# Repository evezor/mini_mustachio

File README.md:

# mini_mustachio

Robotic car project for the Mechanical Mustaches, team #8122 FRC Robotics

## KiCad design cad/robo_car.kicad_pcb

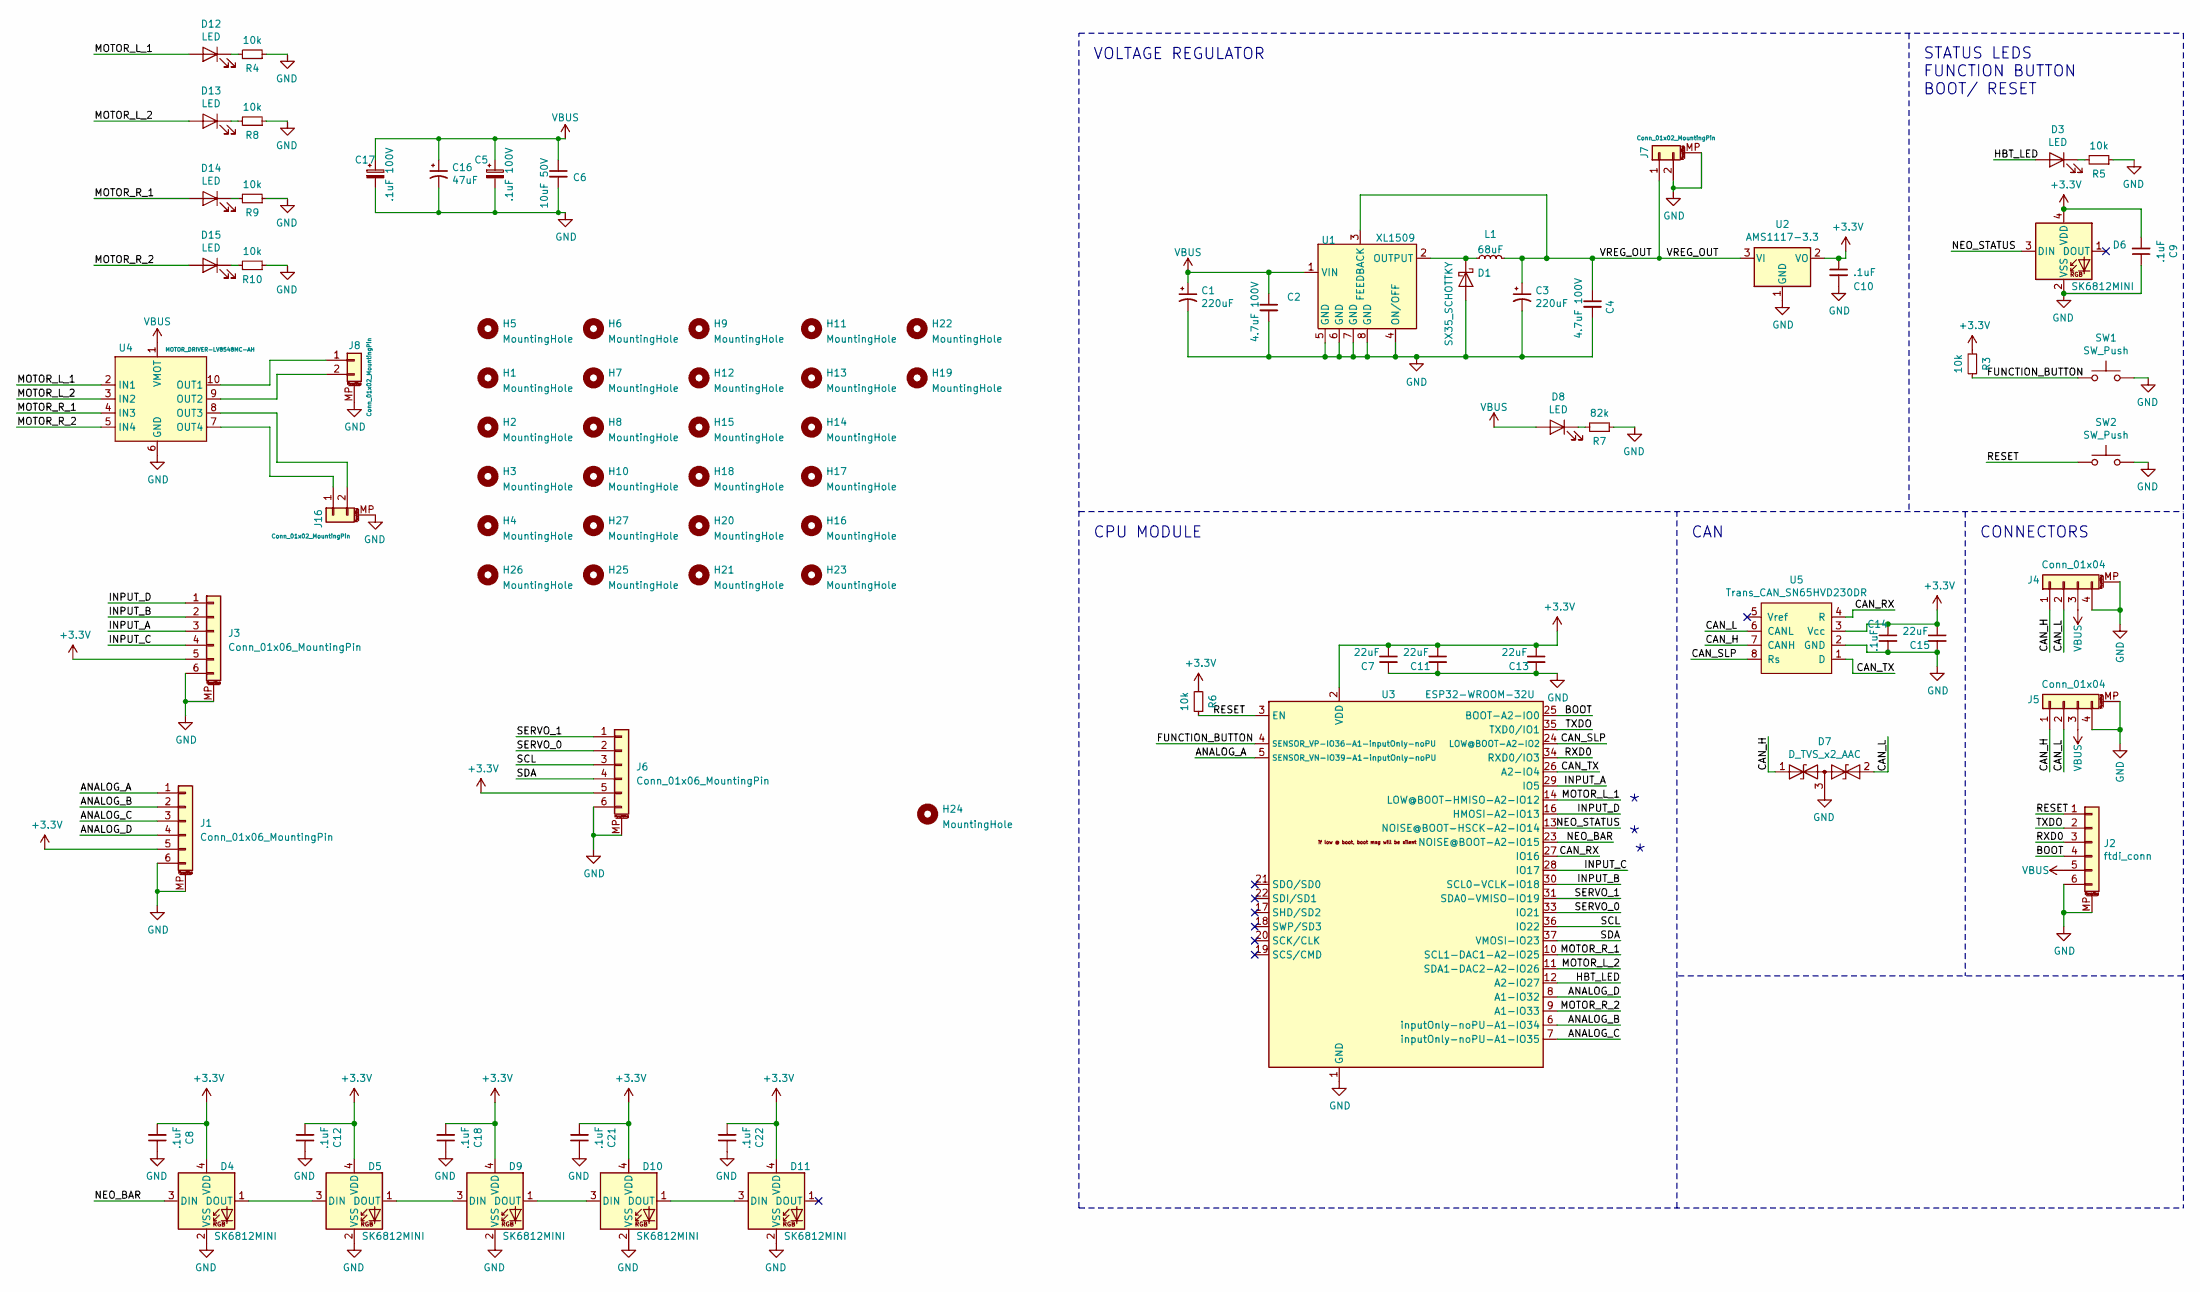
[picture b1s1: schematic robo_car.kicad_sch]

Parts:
C1, C3: 220uF; CP_Elec_10x10.5
C2, C4: 4.7uF 100V; C_0805_2012Metric
C5, C17: .1uF 100V; C_0805_2012Metric
C6: 10uF 50V; C_1206_3216Metric
C7, C11, C13, C15: 22uF; C_0805_2012Metric
C8, C9, C10, C12, C14, C18, C21, C22: .1uF; C_0603_1608Metric
C16: 47uF; CP_Elec_6.3x7.7
D1: SX35_SCHOTTKY; D_SMA
D3, D8, D12, D13, D14, D15: LED; LED_0603_1608Metric
D4, D5, D6, D9, D10, D11: SK6812MINI; LED_SK6812MINI_PLCC4_3.5x3.5mm_P1.75mm
D7: D_TVS_x2_AAC; SOT-23
H1, H2, H3, H4, H5, H6, H7, H8, H9, H10, H11, H12, H13, H14, H15, H16, H17, H18, H19, H20, H25, H26, H27: MountingHole; MountingHole_3.2mm_M3_ISO14580
H21, H22, H23, H24: MountingHole; MountingHole_2.7mm_M2.5_ISO14580
J1, J3, J6: Conn_01x06_MountingPin; TE_84952-6_1x06-1MP_P1.0mm_Horizontal
J2: ftdi_conn; JST_SH_BM06B-SRSS-TB_1x06-1MP_P1.00mm_Vertical
J4: Conn_01x04; JST_PH_B4B-PH-SM4-TB_1x04-1MP_P2.00mm_Vertical
J5: Conn_01x04; JST_PH_S4B-PH-SM4-TB_1x04-1MP_P2.00mm_Horizontal
J7, J8, J16: Conn_01x02_MountingPin; JST_XH_2_VERTICAL
L1: 68uF; INDUCTOR-68uH
R3, R4, R5, R6, R8, R9, R10: 10k; R_0603_1608Metric
R7: 82k; R_0603_1608Metric
SW1, SW2: SW_Push; SWITCH_2x3_SMD_TACTILE_GREEN
U1: XL1509; SOIC-8_3.9x4.9mm_P1.27mm
U2: AMS1117-3.3; SOT-223-3_TabPin2
U3: ESP32-WROOM-32U; ESP32-WROOM-32U_evezor
U4: MOTOR_DRIVER-LV8548MC-AH; SOIC-10_LV8548MC-AH_evezor
U5: Trans_CAN_SN65HVD230DR; CAN-TRANS-SN65HVD230DR

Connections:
+3V3: C7.1, C8.2, C9.2, C10.1, C11.1, C12.2, C13.1, C14.1, C15.1, C18.2, C21.2, C22.2, D4.4 (VDD), D5.4 (VDD), D6.4 (VDD), D9.4 (VDD), D10.4 (VDD), D11.4 (VDD), J1.5, J3.5, J6.5, R3.2, R6.2, U2.2 (VO), U3.2 (VDD), U5.3 (Vcc)
/ANALOG_A: J1.1, U3.5 (SENSOR_VN-IO39-A1-inputOnly-noPU)
/ANALOG_B: J1.2, U3.6 (inputOnly-noPU-A1-IO34)
/ANALOG_C: J1.3, U3.7 (inputOnly-noPU-A1-IO35)
/ANALOG_D: J1.4, U3.8 (A1-IO32)
/BOOT: J2.4, U3.25 (BOOT-A2-IO0)
/CAN_H: D7.1 (A1), J4.1, J5.1, U5.7 (CANH)
/CAN_L: D7.2 (A2), J4.2, J5.2, U5.6 (CANL)
/CAN_RX: U3.27 (IO16), U5.4 (R)
/CAN_SLP: U3.24 (LOW@BOOT-A2-IO2), U5.8 (Rs)
/CAN_TX: U3.26 (A2-IO4), U5.1 (D)
/FUNCTION_BUTTON: R3.1, SW1.1, U3.4 (SENSOR_VP-IO36-A1-inputOnly-noPU)
/HBT_LED: D3.2 (A), U3.12 (A2-IO27)
/INPUT_A: J3.3, U3.29 (IO5)
/INPUT_B: J3.2, U3.30 (SCL0-VCLK-IO18)
/INPUT_C: J3.4, U3.28 (IO17)
/INPUT_D: J3.1, U3.16 (HMOSI-A2-IO13)
/MOTOR_L_1: D12.2 (A), U3.14 (LOW@BOOT-HMISO-A2-IO12), U4.2 (IN1)
/MOTOR_L_2: D13.2 (A), U3.11 (SDA1-DAC2-A2-IO26), U4.3 (IN2)
/MOTOR_R_1: D14.2 (A), U3.10 (SCL1-DAC1-A2-IO25), U4.4 (IN3)
/MOTOR_R_2: D15.2 (A), U3.9 (A1-IO33), U4.5 (IN4)
/NEO_BAR: D4.3 (DIN), U3.23 (NOISE@BOOT-A2-IO15)
/NEO_STATUS: D6.3 (DIN), U3.13 (NOISE@BOOT-HSCK-A2-IO14)
/RESET: J2.1, R6.1, SW2.1, U3.3 (EN)
/RXD0: J2.3, U3.34 (RXD0/IO3)
/SCL: J6.3, U3.36 (IO22)
/SDA: J6.4, U3.37 (VMOSI-IO23)
/SERVO_0: J6.2, U3.33 (IO21)
/SERVO_1: J6.1, U3.31 (SDA0-VMISO-IO19)
/TXDO: J2.2, U3.35 (TXD0/IO1)
/VREG_OUT: C3.1, C4.1, J7.1, L1.1, U1.3 (FEEDBACK), U2.3 (VI)
GND: C1.2, C2.2, C3.2, C4.2, C5.2, C6.2, C7.2, C8.1, C9.1, C10.2, C11.2, C12.1, C13.2, C14.2, C15.2, C16.2, C17.2, C18.1, C21.1, C22.1, D1.2 (A), D4.2 (VSS), D5.2 (VSS), D6.2 (VSS), D7.3 (common), D9.2 (VSS), D10.2 (VSS), D11.2 (VSS), J1.6, J1.MP (MountPin), J2.6, J2.MP (MountPin), J3.6, J3.MP (MountPin), J4.4, J4.MP (MountPin), J5.4, J5.MP (MountPin), J6.6, J6.MP (MountPin), J7.2, J7.MP (MountPin), J8.MP (MountPin), J16.MP (MountPin), R4.1, R5.1, R7.1, R8.1, R9.1, R10.1, SW1.2, SW2.2, U1.4 (ON/OFF), U1.5 (GND), U1.6 (GND), U1.7 (GND), U1.8 (GND), U2.1 (GND), U3.1 (GND), U3.15 (GND), U3.38 (GND), U3.39 (GND), U4.6 (GND), U5.2 (GND)
unnamed: D1.1 (K), L1.2, U1.2 (OUTPUT)
unnamed: D3.1 (K), R5.2
unnamed: D4.1 (DOUT), D5.3 (DIN)
unnamed: D5.1 (DOUT), D9.3 (DIN)
unnamed: D8.1 (K), R7.2
unnamed: D10.1 (DOUT), D11.3 (DIN)
unnamed: D9.1 (DOUT), D10.3 (DIN)
unnamed: D12.1 (K), R4.2
unnamed: D13.1 (K), R8.2
unnamed: D14.1 (K), R9.2
unnamed: D15.1 (K), R10.2
unnamed: J8.1, U4.10 (OUT1)
unnamed: J8.2, U4.9 (OUT2)
unnamed: J16.1, U4.7 (OUT4)
unnamed: J16.2, U4.8 (OUT3)
VBUS: C1.1, C2.1, C5.1, C6.1, C16.1, C17.1, D8.2 (A), J2.5, J4.3, J5.3, U1.1 (VIN), U4.1 (VMOT)

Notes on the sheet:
VOLTAGE REGULATOR
CPU MODULE
CAN
STATUS LEDS FUNCTION BUTTON BOOT/ RESET
CONNECTORS

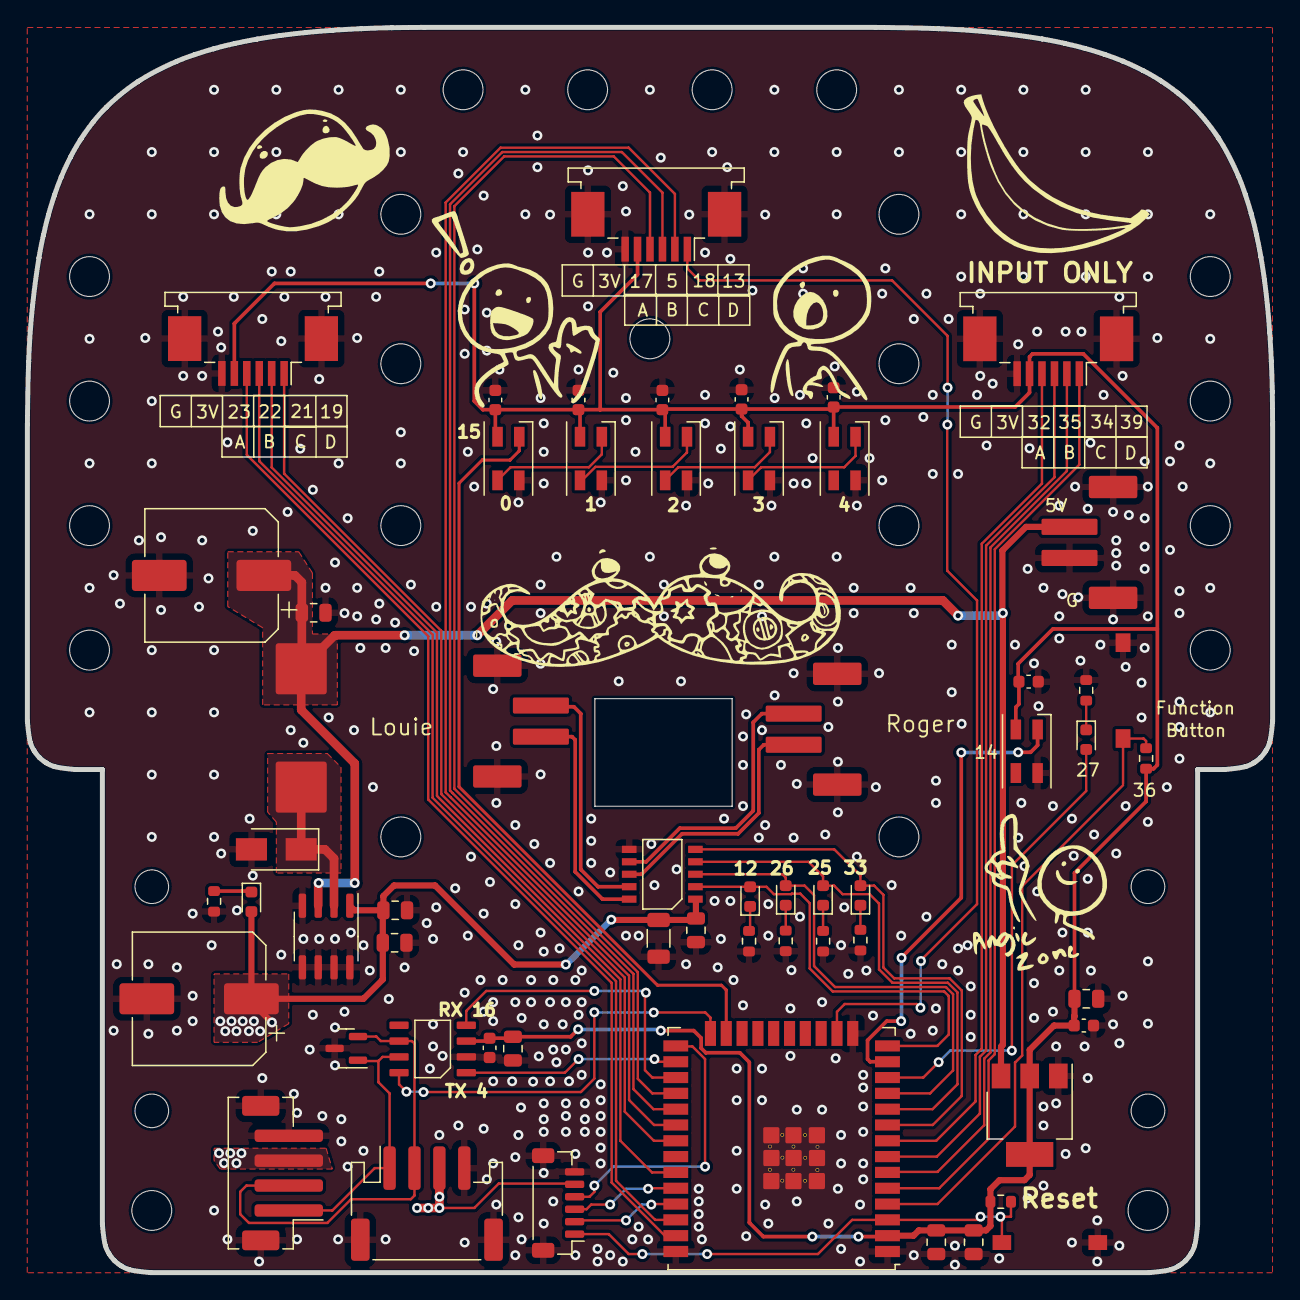
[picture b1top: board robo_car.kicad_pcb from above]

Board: 2 copper layers, 100.0 x 100.0 mm, 85 parts (0 on the bottom side), 48 nets.

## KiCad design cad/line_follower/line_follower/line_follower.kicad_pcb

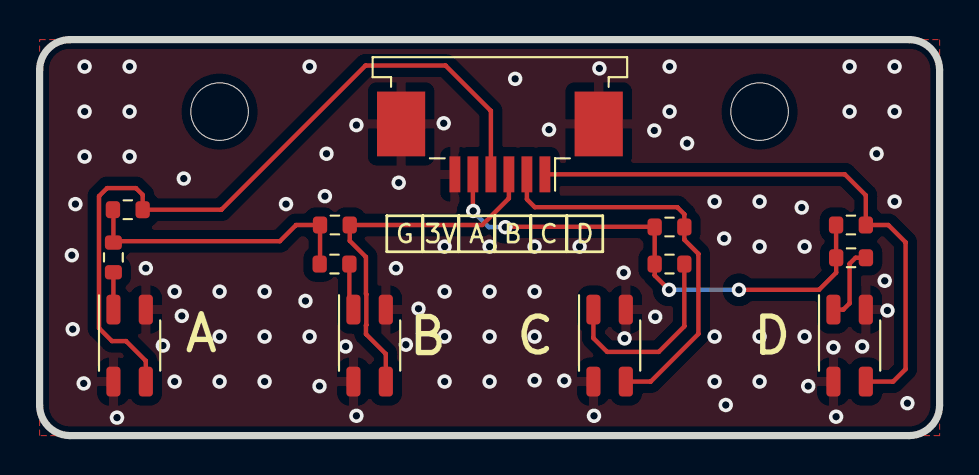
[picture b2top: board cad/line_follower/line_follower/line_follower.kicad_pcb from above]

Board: 2 copper layers, 50.0 x 22.0 mm, 15 parts (0 on the bottom side), 10 nets.

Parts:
H1, H2: MountingHole; MountingHole_3.2mm_M3_ISO14580
J9: Conn_01x06_MountingPin; TE_84952-6_1x06-1MP_P1.0mm_Horizontal
R3, R6, R9, R12: R100; R_0603_1608Metric
R5, R8, R10, R13: 10K; R_0603_1608Metric
U1, U2, U3, U4: QRE1113GR; OnSemi_CASE100CY

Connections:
+3V3: J9.5, R3.1, R5.1, R6.1, R8.1, R9.1, R10.1, R12.1, R13.1
/Button A: J9.4, R13.2, U4.3
/Button B: J9.3, R10.2, U3.3
/Button C: J9.2, R5.2, U1.3
/Button D: J9.1, R8.2, U2.3
GND: J9.6, J9.MP (MountPin), U1.2 (K), U1.4, U2.2 (K), U2.4, U3.2 (K), U3.4, U4.2 (K), U4.4
unnamed: R3.2, U1.1 (A)
unnamed: R6.2, U2.1 (A)
unnamed: R9.2, U3.1 (A)
unnamed: R12.2, U4.1 (A)

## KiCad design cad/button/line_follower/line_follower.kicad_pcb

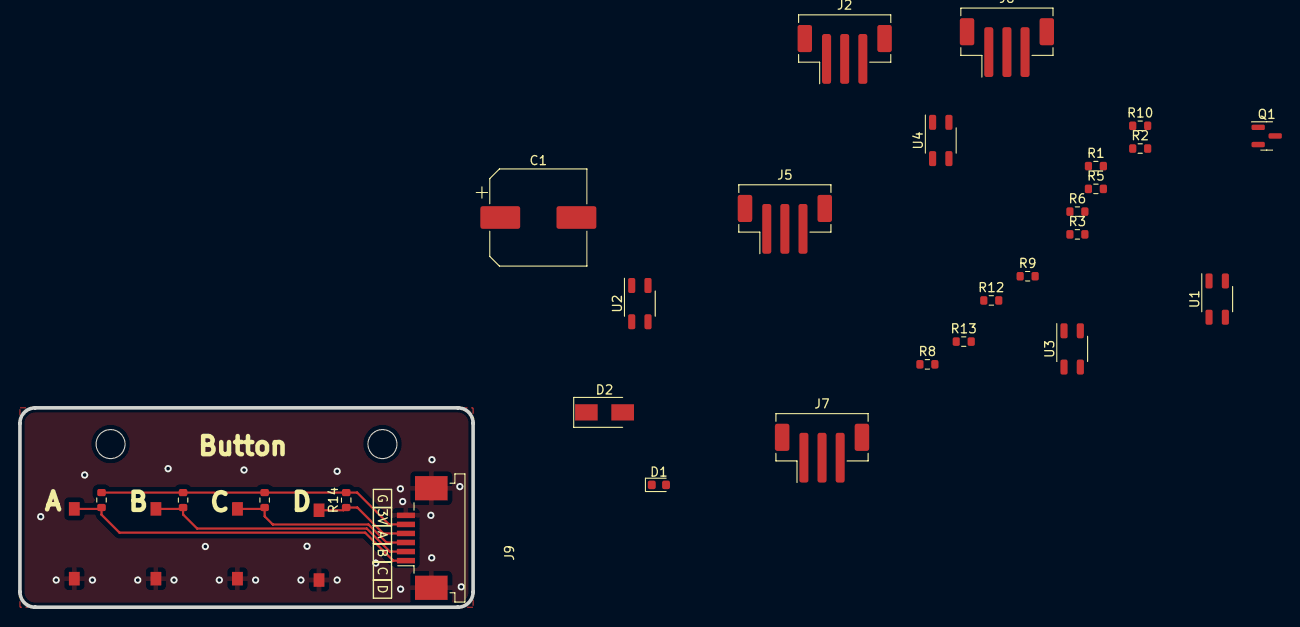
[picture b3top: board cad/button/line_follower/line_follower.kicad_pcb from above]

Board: 2 copper layers, 50.0 x 22.0 mm, 33 parts (0 on the bottom side), 18 nets.

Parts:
C1: 220uF; CP_Elec_10x12.5
D1: led_g; LED_0603_1608Metric
D2: SX35_SCHOTTKY; D_SMA
H1, H2: MountingHole; MountingHole_3.2mm_M3_ISO14580
J2, J5, J7, J8: Conn_01x03; JST_PH_B3B-PH-SM4-TB_1x03-1MP_P2.00mm_Vertical
J9: Conn_01x06_MountingPin; TE_84952-6_1x06-1MP_P1.0mm_Horizontal
Q1: LOW PWR FET; SOT-23
R1, R2, R4, R7, R11, R14: 10k; R_0603_1608Metric
R3, R6, R9, R12: R100; R_0603_1608Metric
R5, R8, R10, R13: 10K; R_0603_1608Metric
SW1, SW2, SW3, SW4: SW_Push; SWITCH_2x3_SMD_TACTILE_GREEN
U1, U2, U3, U4: QRE1113GR; OnSemi_CASE100CY

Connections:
+3V3: J2.2, J5.2, J7.2, J8.2, J9.5, R3.1, R4.2, R5.1, R6.1, R7.2, R8.1, R9.1, R10.1, R11.2, R12.1, R13.1, R14.2
/Button A: J9.1, R4.1, SW1.1
/Button B: J9.2, R7.1, SW2.1
/Button C: J9.3, R11.1, SW3.1
/Button D: J9.4, R14.1, SW4.1
/FAN: Q1.1 (G), R1.2, R2.2
/PROBE: J2.1, J5.1, J7.1, J8.1
GND: D1.1 (K), J2.3, J2.MP (MountPin), J5.3, J5.MP (MountPin), J7.3, J7.MP (MountPin), J8.3, J8.MP (MountPin), J9.6, J9.MP (MountPin), Q1.2 (S), R2.1, SW1.2, SW2.2, SW3.2, SW4.2, U1.2 (K), U1.4, U2.2 (K), U2.4, U3.2 (K), U3.4, U4.2 (K), U4.4
unnamed: D1.2 (A), R1.1
unnamed: D2.2 (A), Q1.3 (D)
unnamed: R3.2, U1.1 (A)
unnamed: R5.2, U1.3
unnamed: R6.2, U2.1 (A)
unnamed: R8.2, U2.3
unnamed: R9.2, U3.1 (A)
unnamed: R10.2, U3.3
unnamed: R12.2, U4.1 (A)
unnamed: R13.2, U4.3

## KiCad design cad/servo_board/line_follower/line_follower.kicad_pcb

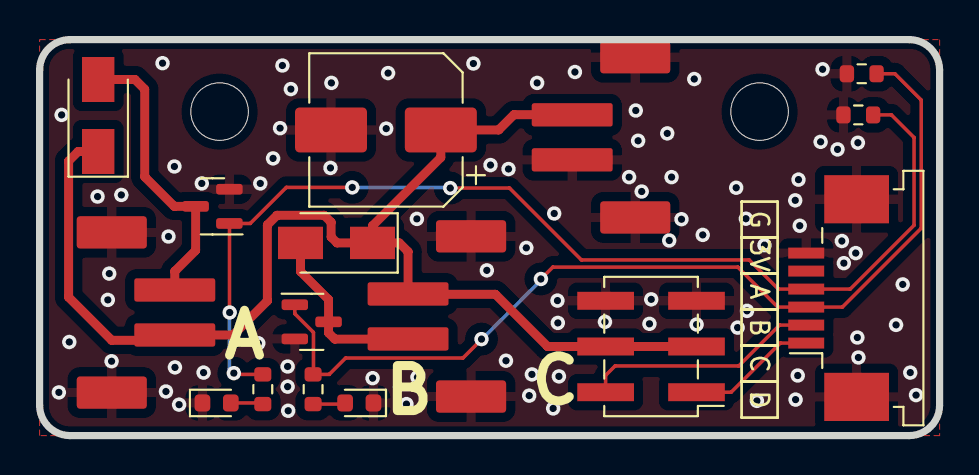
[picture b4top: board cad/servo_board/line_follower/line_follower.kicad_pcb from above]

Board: 2 copper layers, 50.0 x 22.0 mm, 18 parts (0 on the bottom side), 10 nets.

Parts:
C1: 220uF; CP_Elec_8x6.5
D1, D3: led_g; LED_0603_1608Metric
D2, D4: SX35_SCHOTTKY; D_SMA
H1, H2: MountingHole; MountingHole_3.2mm_M3_ISO14580
J1, J2, J6: Conn_01x02; JST_XH_2_VERTICAL
J4: Servo Header x2; PinHeader_2x03_P2.54mm_Vertical_SMD
J9: Conn_01x06_MountingPin; TE_84952-6_1x06-1MP_P1.0mm_Horizontal
Q1, Q2: LOW PWR FET; SOT-23
R1, R2, R3, R4: 10k; R_0603_1608Metric

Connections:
+VDC: C1.1, D2.1 (K), D4.1 (K), J1.1, J2.1, J4.3, J4.4, J6.1
/SERVO_2: J4.2, J9.2
/SERVO_4: J4.1, J9.1
/Thing 1: J9.4, Q1.1 (G), R1.2, R2.2
/Thing 2: J9.3, Q2.1 (G), R3.2, R4.2
GND: C1.2, D1.1 (K), D3.1 (K), J1.MP (MountPin), J2.MP (MountPin), J4.5, J4.6, J6.2, J6.MP (MountPin), J9.6, J9.MP (MountPin), Q1.2 (S), Q2.2 (S), R2.1, R4.1
unnamed: D1.2 (A), R1.1
unnamed: D2.2 (A), J1.2, Q1.3 (D)
unnamed: D3.2 (A), R3.1
unnamed: D4.2 (A), J2.2, Q2.3 (D)

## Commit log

2022-05-11 legit, first commit :)
2022-05-13 Traces started, chicken cooking
2022-05-16 Handy highway comes in from the other left *beep beep*
2022-05-16 super secret secret follows the line
2022-05-19 Noise complaint, V cops on the way
2022-05-24 Roger, rodger? Wait it's Ralphie!
2022-05-26 Dapper drawings, forward and behindward!
2022-06-06 github gary gets groovy garbage :)
2022-06-11 Olivia Attempts Andrewism, and Abolishes Her Awesome Highway
2022-06-11 Andrew Puts a Traffic Cone on Olivia's Happy Highway
2022-06-11 Sleepy Olivia Draws Lines
2022-06-12 More awake Olivia fixes some things
2022-06-12 lots of vias, maybe too much?
2022-06-12 Andrew wants what!?!?! 5 more boards???
2022-06-13 Little tiny baby commit where i push the little tiny baby changes
2022-06-21 Half of the 2nd floor built, remodeling in progress
2022-06-23 Mega monster huge scary big board 4.0 big scary there's like 4 pieces but its actually not that scary huge hugh mungus big board also mousey bites
2022-06-24 tracey thingies
2022-06-24 Big Kahuna finished, winrar zippy files are funny
2022-07-02 codey code code this should work i think
2022-07-02 messy mess hopefully less mess, maybe :)
2022-07-12 I fixed the label for the pin we changed cause bad label is bad
